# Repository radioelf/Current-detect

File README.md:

# Current-detect
Deteción de corriente electrica (consumo de una carga), KICAD Version: 5.99.0, release build

Creative Commons License Disclaimer

UNLESS OTHERWISE MUTUALLY AGREED TO BY THE PARTIES IN WRITING, LICENSOR OFFERS THE WORK AS-IS AND MAKES NO 
REPRESENTATIONS OR WARRANTIES OF ANY KIND CONCERNING THE WORK, EXPRESS, IMPLIED, STATUTORY OR OTHERWISE, 
INCLUDING, WITHOUT LIMITATION, WARRANTIES OF TITLE, MERCHANTIBILITY, FITNESS FOR A PARTICULAR PURPOSE, 
NONINFRINGEMENT, OR THE ABSENCE OF LATENT OR OTHER DEFECTS, ACCURACY, OR THE PRESENCE OF ABSENCE OF ERRORS, 
WHETHER OR NOT DISCOVERABLE. SOME JURISDICTIONS DO NOT ALLOW THE EXCLUSION OF IMPLIED WARRANTIES, 
SO SUCH EXCLUSION MAY NOT APPLY TO YOU. EXCEPT TO THE EXTENT REQUIRED BY APPLICABLE LAW, IN NO EVENT 
WILL LICENSOR BE LIABLE TO YOU ON ANY LEGAL THEORY FOR ANY SPECIAL, INCIDENTAL, CONSEQUENTIAL, PUNITIVE 
OR EXEMPLARY DAMAGES ARISING OUT OF THIS LICENSE OR THE USE OF THE WORK, EVEN IF LICENSOR HAS BEEN ADVISED 
OF THE POSSIBILITY OF SUCH DAMAGES.

http://creativecommons.org/licenses/by-sa/3.0/

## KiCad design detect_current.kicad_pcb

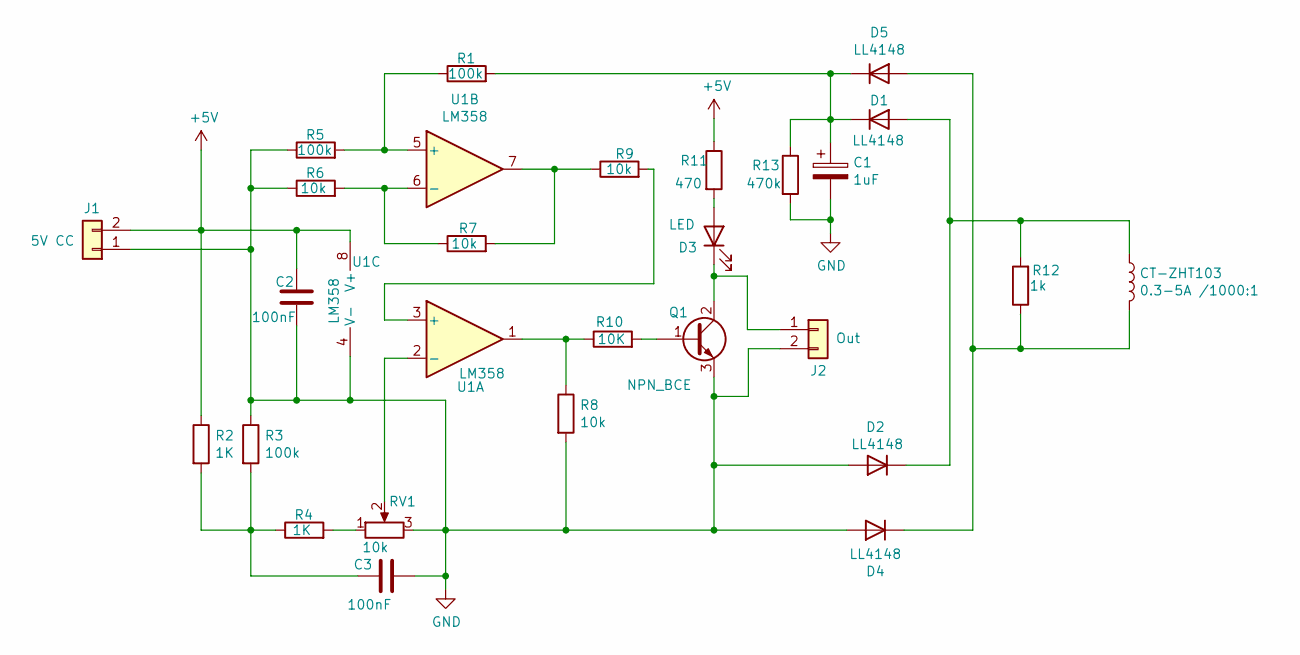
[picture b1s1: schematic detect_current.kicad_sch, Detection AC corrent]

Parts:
C1: 1uF; CP_EIA-3528-12_Kemet-T
C2, C3: 100nF; C_0805_2012Metric
CT-ZHT103: 0.3-5A /1000:1; L_Axial_L9.5mm_D4.0mm_P12.70mm_Horizontal_Fastron_SMCC
D1, D2, D4, D5: LL4148; D_MiniMELF
D3: LED; LED_0805_2012Metric
J1: 5V CC; JST_NV_B02P-NV_1x02_P5.00mm_Vertical
J2: Out; JST_NV_B02P-NV_1x02_P5.00mm_Vertical
Q1: NPN_BCE; TSOT-23
R1, R3, R5: 100k; R_0805_2012Metric
R2, R4: 1K; R_0805_2012Metric
R6, R7, R8, R9: 10k; R_0805_2012Metric
R10: 10K; R_0805_2012Metric
R11: 470; R_0805_2012Metric
R12: 1k; R_0805_2012Metric
R13: 470k; R_0805_2012Metric
RV1: 10k; Potentiometer_Bourns_3296Y_Vertical
U1: LM358; SOP-8_3.9x4.9mm_P1.27mm

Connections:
+5V: C2.2, J1.2, R2.1, R11.1, U1.8 (V+)
GND: C1.2, C2.1, C3.2, D2.2 (A), D4.2 (A), J1.1, J2.2, Q1.3 (E), R3.1, R5.1, R6.1, R8.2, R13.2, RV1.3, U1.4 (V-)
unnamed: C1.1, D1.1 (K), D5.1 (K), R1.2, R13.1
unnamed: C3.1, R2.2, R3.2, R4.1
unnamed: CT-ZHT103.1, D1.2 (A), D2.1 (K), R12.2
unnamed: CT-ZHT103.2, D4.1 (K), D5.2 (A), R12.1
unnamed: D3.1 (K), J2.1, Q1.2 (C)
unnamed: D3.2 (A), R11.2
unnamed: Q1.1 (B), R10.2
unnamed: R1.1, R5.2, U1.5 (+)
unnamed: R4.2, RV1.1
unnamed: R6.2, R7.1, U1.6 (-)
unnamed: R7.2, R9.1, U1.7
unnamed: R9.2, U1.3 (+)
unnamed: R8.1, R10.1, U1.1
unnamed: RV1.2, U1.2 (-)

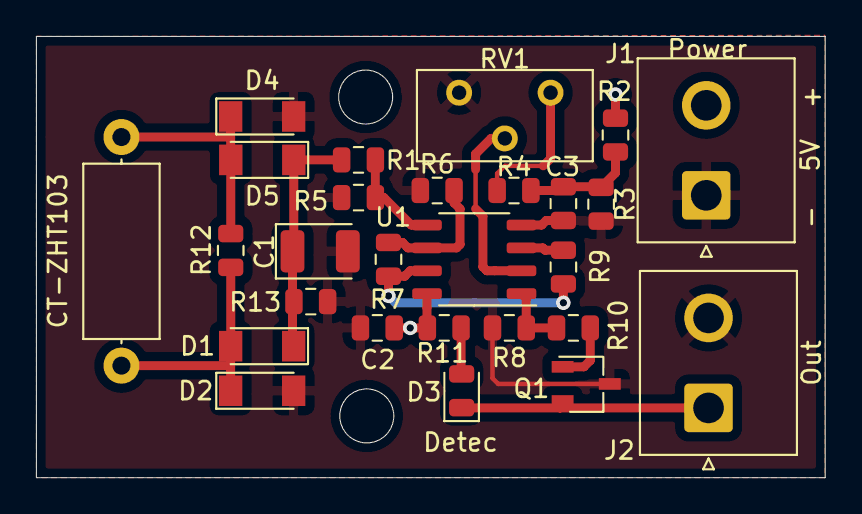
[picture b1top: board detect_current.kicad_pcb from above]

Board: 2 copper layers, 43.8 x 24.5 mm, 27 parts (0 on the bottom side), 16 nets.

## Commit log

2020-07-21 /gerber
2020-07-21 Update detect_current.kicad_pcb-bak
2020-07-21 Update detect_current.kicad_sch-bak
